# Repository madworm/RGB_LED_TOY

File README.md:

RGB_LED_TOY
===========

LAYOUT FILES: LED ring board with 8 WS2812B RGB LEDs driven by an ATmega168-20AU TQFP-32 7x7 micro controller. KICAD and Gerber files.

You will find code for this project in [this](https://github.com/madworm/rgb_led_toy_test) repository.

---

Before having PC-boards made, please make sure you know about your manufacturer's peculiarities!
Especially drill-sizes and their tolerances may vary too much and give you trouble.

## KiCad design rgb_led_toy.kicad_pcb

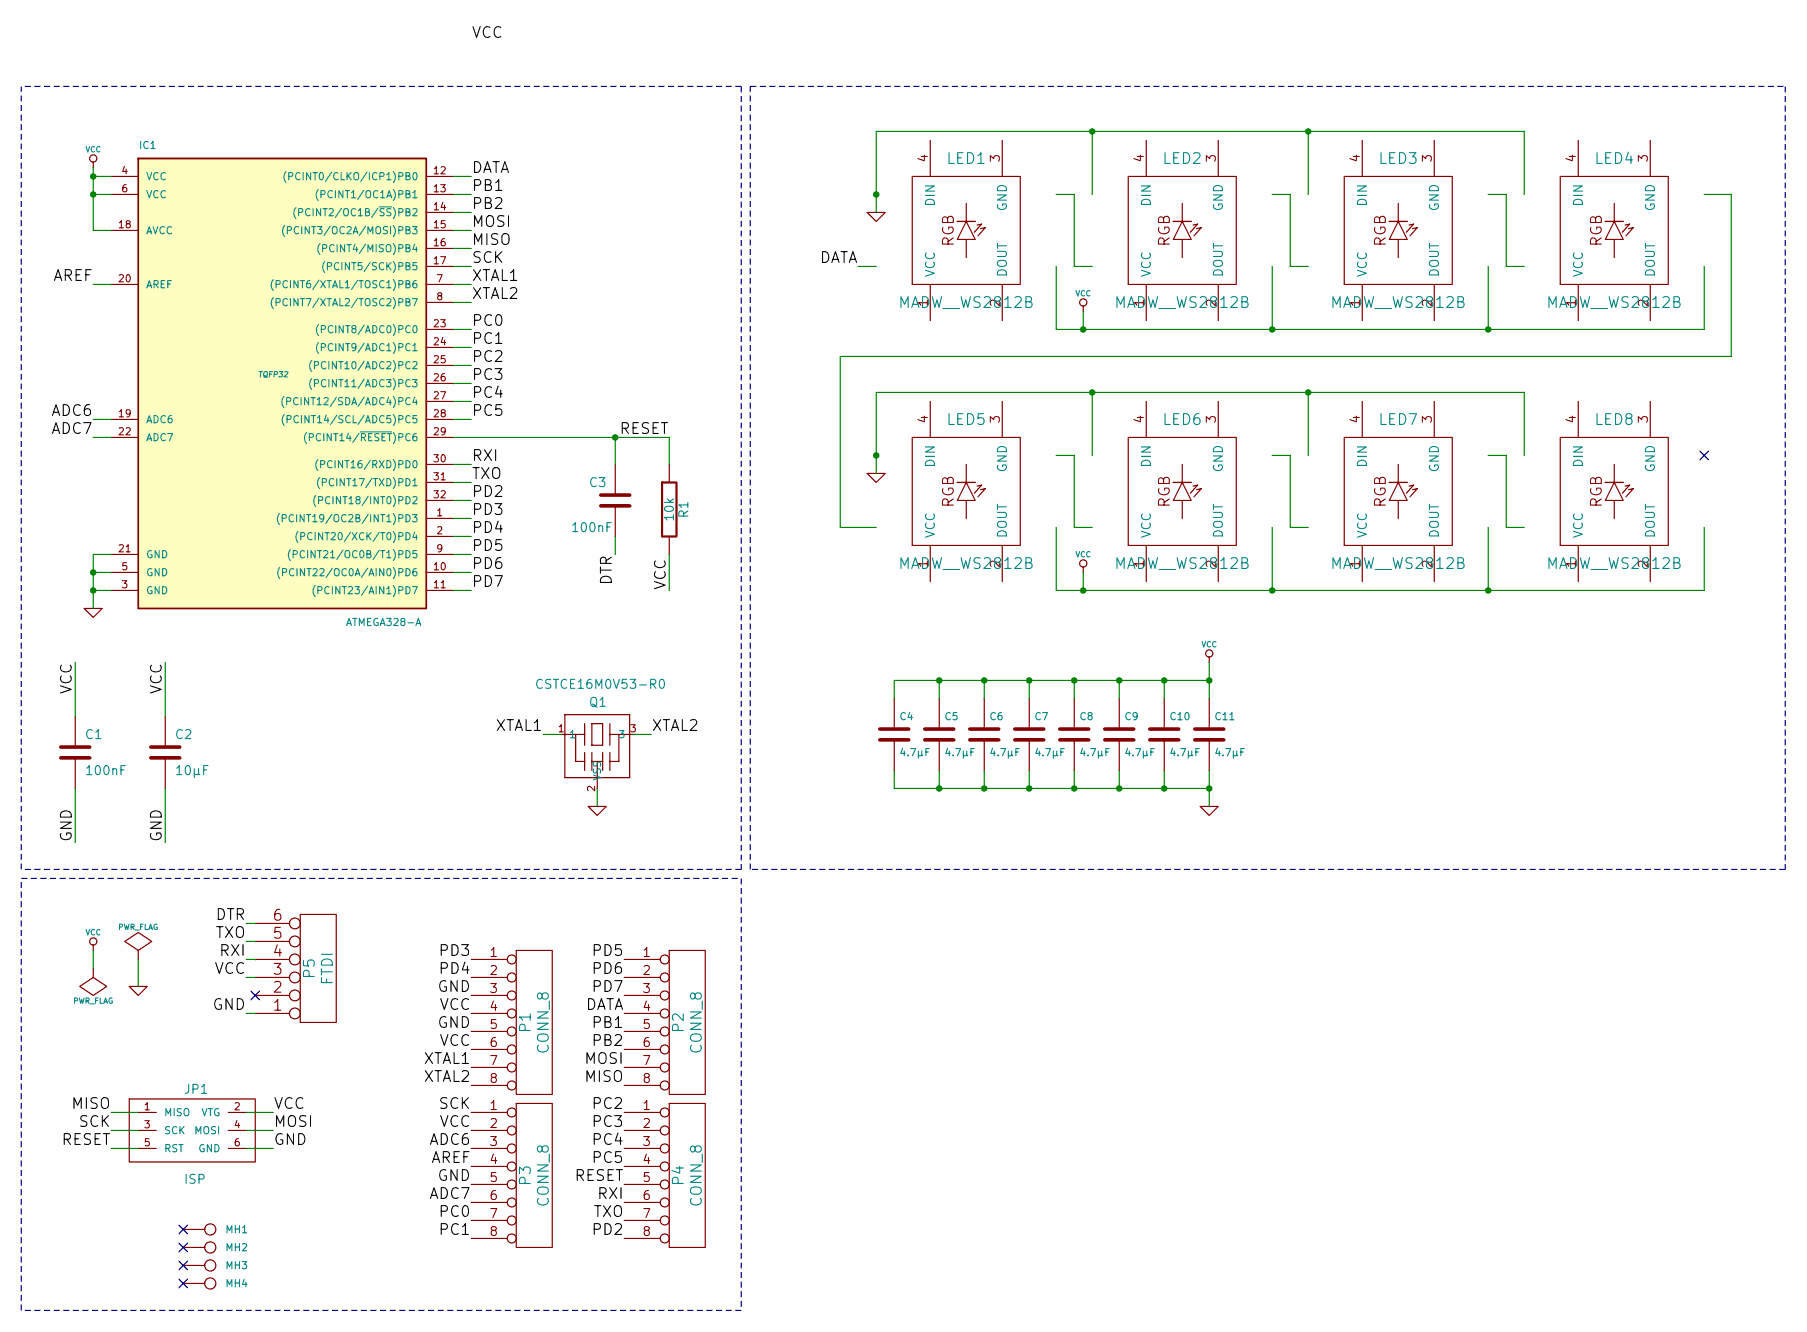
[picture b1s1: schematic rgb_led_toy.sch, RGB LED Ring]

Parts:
C1, C3: 100nF
C2: 10µF
C4, C5, C6, C7, C8, C9, C10, C11: 4.7µF
IC1: ATMEGA328-A; TQFP32
JP1: ISP
LED1, LED2, LED3, LED4, LED5, LED6, LED7, LED8: MADW__WS2812B
MH1, MH2, MH3, MH4: CONN_1
P1, P2, P3, P4: CONN_8
P5: FTDI
Q1: CSTCE16M0V53-R0; murata-resonators-CSTLA_T
R1: 10k

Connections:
/ADC6: IC1.19 (ADC6), P3.3
/ADC7: IC1.22 (ADC7), P3.6
/AREF: IC1.20 (AREF), P3.4
/DATA: IC1.12 ((PCINT0/CLKO/ICP1)PB0), LED1.4 (DIN), P2.4
/DTR: C3.2, P5.6
/MISO: IC1.16 ((PCINT4/MISO)PB4), JP1.1 (MISO), P2.8
/MOSI: IC1.15 ((PCINT3/OC2A/MOSI)PB3), JP1.4 (MOSI), P2.7
/PB1: IC1.13 ((PCINT1/OC1A)PB1), P2.5
/PB2: IC1.14 ((PCINT2/OC1B/~SS~)PB2), P2.6
/PC0: IC1.23 ((PCINT8/ADC0)PC0), P3.7
/PC1: IC1.24 ((PCINT9/ADC1)PC1), P3.8
/PC2: IC1.25 ((PCINT10/ADC2)PC2), P4.1
/PC3: IC1.26 ((PCINT11/ADC3)PC3), P4.2
/PC4: IC1.27 ((PCINT12/SDA/ADC4)PC4), P4.3
/PC5: IC1.28 ((PCINT14/SCL/ADC5)PC5), P4.4
/PD2: IC1.32 ((PCINT18/INT0)PD2), P4.8
/PD3: IC1.1 ((PCINT19/OC2B/INT1)PD3), P1.1
/PD4: IC1.2 ((PCINT20/XCK/T0)PD4), P1.2
/PD5: IC1.9 ((PCINT21/OC0B/T1)PD5), P2.1
/PD6: IC1.10 ((PCINT22/OC0A/AIN0)PD6), P2.2
/PD7: IC1.11 ((PCINT23/AIN1)PD7), P2.3
/RESET: C3.1, IC1.29 ((PCINT14/~RESET~)PC6), JP1.5 (RST), P4.5, R1.1
/RXI: IC1.30 ((PCINT16/RXD)PD0), P4.6, P5.4
/SCK: IC1.17 ((PCINT5/SCK)PB5), JP1.3 (SCK), P3.1
/TXO: IC1.31 ((PCINT17/TXD)PD1), P4.7, P5.5
/XTAL1: IC1.7 ((PCINT6/XTAL1/TOSC1)PB6), P1.7, Q1.1
/XTAL2: IC1.8 ((PCINT7/XTAL2/TOSC2)PB7), P1.8, Q1.3
GND: C1.2, C2.2, C4.2, C5.2, C6.2, C7.2, C8.2, C9.2, C10.2, C11.2, IC1.3 (GND), IC1.5 (GND), IC1.21 (GND), JP1.6 (GND), LED1.3 (GND), LED2.3 (GND), LED3.3 (GND), LED4.3 (GND), LED5.3 (GND), LED6.3 (GND), LED7.3 (GND), LED8.3 (GND), P1.3, P1.5, P3.5, P5.1, Q1.2 (VSS)
Net-<LED1-Pad2>: LED1.2 (DOUT), LED2.4 (DIN)
Net-<LED2-Pad2>: LED2.2 (DOUT), LED3.4 (DIN)
Net-<LED3-Pad2>: LED3.2 (DOUT), LED4.4 (DIN)
Net-<LED4-Pad2>: LED4.2 (DOUT), LED5.4 (DIN)
Net-<LED5-Pad2>: LED5.2 (DOUT), LED6.4 (DIN)
Net-<LED6-Pad2>: LED6.2 (DOUT), LED7.4 (DIN)
Net-<LED7-Pad2>: LED7.2 (DOUT), LED8.4 (DIN)
VCC: C1.1, C2.1, C4.1, C5.1, C6.1, C7.1, C8.1, C9.1, C10.1, C11.1, IC1.4 (VCC), IC1.6 (VCC), IC1.18 (AVCC), JP1.2 (VTG), LED1.1 (VCC), LED2.1 (VCC), LED3.1 (VCC), LED4.1 (VCC), LED5.1 (VCC), LED6.1 (VCC), LED7.1 (VCC), LED8.1 (VCC), P1.4, P1.6, P3.2, P5.3, R1.2

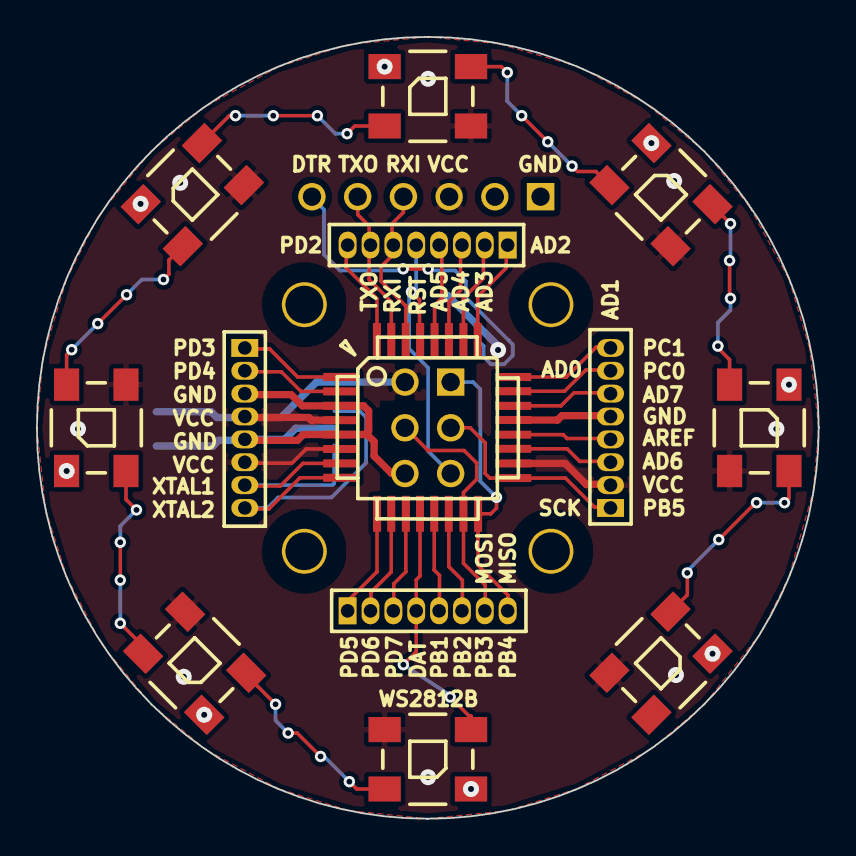
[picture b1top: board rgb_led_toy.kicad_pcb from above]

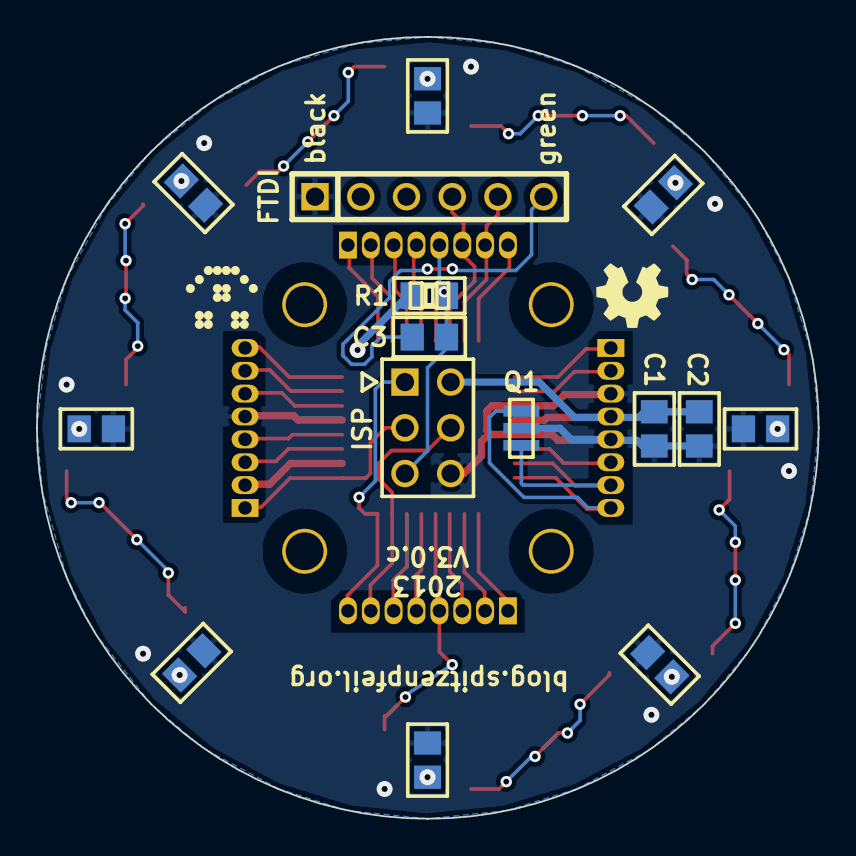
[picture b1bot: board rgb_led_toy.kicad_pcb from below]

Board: 2 copper layers, 43.4 x 43.4 mm, 34 parts (17 on the bottom side), 36 nets.

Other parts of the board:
G1: OSHW-logo_silkscreen_4mm
G2: LED_smile_silkscreen_4mm

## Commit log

2010-01-05 init
2010-01-05 upgraded to V.1.2: voltage regulator, isp_e jumpers.
2010-01-05 modified: rgb_led_toy-schematic.pdf modified: rgb_led_toy-schematic.svg modified: rgb_led_toy.000 modified: rgb_led_toy.bak modified: rgb_led_toy.brd modified: rgb_led_toy.cache.dcm modified: rgb_led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
2010-01-05 fixed silkscreen error. tantalum caps are polarized and need a + mark
2010-01-06 Fixed some silkscreen errors again.
2010-01-06 Added copper fill. Upped to V.1.21
2010-01-06 Changed the zone filling a bit.
2010-01-06 'Exclude Edges_Pcb layer' is necessary to keep the DRC bot happy.
2010-01-06 Another attempt to please the DRC bot. KICAD produces little tiny blobs and gaps in the copper fill that the bot doesn't like.
2010-01-06 This time the BatchPCB DRC bot is happy. Ordered 2 prototypes of V.1.21
2010-01-06 The drill file format was wrong it seemed. Changed to: units: inches, zeros format: suppress leading zeros, precision: 2:4, drill origin: absolute
2010-02-19 new file: rgb_led_toy-BOM.ods.zip new file: rgb_led_toy-BOM.txt
    added BOM
2010-03-02 modified: rgb_led_toy-BOM.ods.zip
2010-04-01 modified: rgb_led_toy-BOM.ods.zip modified: rgb_led_toy-BOM.txt
    updates
2010-05-17 modified: rgb_led_toy-BOM.ods.zip
    DONE. All parts are here ;-)
2010-08-01 Added a readme file with some info.
2010-09-02 V 1.22 test. Added another set of 3 resistors for more current (I hope). Also remove the ISP_E jumpers. ISP flashing worked with the jumpers bridged last time, so they're useless.
2010-09-05 V1.23 - fixed the LED footprint/wiring for the JELEDHK RGB LEDs (PLCC6 5050). - added the 'more light hack' (3 more resistors) etc etc. - replaced the 6pin headers with 8pin ones - added VCC to the '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
2011-10-05 Renamed the schematic files for consistency with other projects.
2011-10-08 Corrected some .gvp files due to folder renaming.
2011-12-19 Testing feasibility of a ring with 3x MBI5168.
2011-12-20 Version 2.0 alpha with just one MBI5168.
    Let's see if color balancing can be done with software dot correction.
2011-12-20 Fixd the LED numbering scheme.
2011-12-20 Did some 'important' updates to the silkscreen.
2011-12-20 Fixed overlapping text on silkscreen. What else?
2011-12-20 As it's winter now (started to snow today), I added a winter themed .gvp
2011-12-21 Routed V2.0 beta with 3x MBI5168 instead of just one + 3 P-FETs.
2011-12-21 Undid some auto-router badness.
2011-12-23 Beautification of the schematic. No functional changes.
2011-12-27 Added (+) text to the silkscreen for all decoupling caps.
    Seems like I won't get 1206 10µF ceramic caps for cheap this time,
    so I might use up my stash of A3216 (metric) tantalum caps (polarized).
2011-12-27 Replaced the (+) with a simple 'dot'. Looks better, less clutter.
2012-01-06 Added a dual PLCC6-5050 / PLCC2 LED footprint + board rev: 2.0.c
2012-01-06 Moved 2 logos a bit.
2012-01-06 Shifted things around a bit.
2012-01-06 Added another 8x 0805 LEDs (just all on/off). Board rev: 2.0.d
2012-01-07 Silkscreen tweaks... moving vias around...
2012-01-07 Moved the auxiliary 0805 LEDs to a hardware PWM pin.
2012-01-10 Fixed the swapped GND / DTR pins on the FTDI header.
    This error was introduced in 80289ae848025eb0ddf43d037901b7deda3aad72.
    Commit a7f8c3d605fc21b7360958f8f994f2175ff54792 is still OK, but a
    different board revision as well.
2012-01-11 Moved 'led0' to a hardware PWM pin that is actually free to use.
2012-01-11 Added some weird stuff to the silkscreen again.
2012-01-14 Miniscule visual tweak to the schematic.
2012-01-15 Minor mods + added 'Lord Helmet' as well ;-)
2012-03-14 Added a BOM/assembly .pdf file (hybrid mode).
2012-03-14 Fixed a line-width problem.
2012-03-14 Added a note regarding RGB LEDs and 250°C
2012-03-17 Added an alternative for the MBI5168 to the BOM: STP08CP05MTR
2012-03-17 Corrected the page format from "letter" to "A4" for the BOM file.
2012-04-06 Added 'push.sh'
2012-04-26 Upgraded the BOM .pdf file.
2012-05-08 Added the TSOP38238 for IR reception to INT0 + some silkscreen art.
2012-05-09 Silkscreen tweaks.
2012-05-09 Shifted a header a bit + shell-script mods.
2012-05-09 Removed useless line in .gvp files. Why does it store that...
2012-05-09 Fixed a 'silly trace'.
2012-05-09 Fixed the back silkscreen. As usual right after the order...
2012-05-09 Updated the bom.
2012-05-09 TSOP38238 rotated 180° so it can be flat on the board looking upwards.
2012-05-09 Upped the version to 2.0.f
2012-05-10 Shifted a few parts to fix the silkscreen.
2012-05-10 Moved a via due to silkscreen interference.
2012-05-11 Moved the OE pin to a hardware PWM pin (PD5).
2012-05-11 Moved the OE pin to TIMER2 PWM (PD3) for increased frequency.
2012-05-12 Added 3x fire symbols to the silkscreen (LED drivers do get hot).
2012-05-12 Added a no-net copper pour to spread the heat a bit better.
2012-05-12 Redid the copper pour outline. Should panelize better.
2012-05-13 'power'-net via changed from 35:25 to 35:20 (wider anular ring).
2012-05-17 Added the MBI5167 as an alternative to the BOM.
2012-05-17 Forgot an empty line.
2012-05-24 Experimenting with 'gerbmerge' and panelization.
2012-05-24 Added drill holes in the break-away tabs.
2012-05-31 Tweaks.
    Forgot to give unique names to the break-away drill holes.
    One mounting hole wasn't named correctly.
2012-06-02 Filled .gitignore with meaningful entries.
2012-06-02 Removed files now covered by .gitignore
2012-06-02 Updated .gitignore
2012-07-22 Added some assembly-tips.
2012-07-26 Updated 'assembly-tips.txt'
2012-09-03 Cleaned up the .gvp files...
2012-11-25 gerbmerge: + missing fiducial. Don't use silkscreen / mask subtraction in KiCad.
2013-01-17 Added README.md
2013-01-23 Increased drill size for pin-headers to 40mil.
    Did NOT recreate gerber files!
2013-01-23 Recreated the gerber files (40mil drill size issue).
2013-01-23 Changed library path, so it doesn't use a symlink anymore.
2013-02-11 Added a step-by-step assembly guide for V2.1 boards. See Docs folder.
2013-04-23 Updated 'README.md'
2013-05-13 Updated assembly instructions for V2.1 boards.
2013-06-27 Renamed a file in ./Docs/ folder.
2013-06-28 Converted to new kicad board format.
2013-09-20 V3.0 doodles.
2013-09-21 Might be a first working V3.0
2013-09-21 Some tweaks.
2013-09-21 LED-string now goes clockwise. Added 1.27mm headers for all MCU pins.
2013-09-22 Tweaks: silkscreen, copper p. cutouts, 8mil min trace width, 16MHz reso.
2013-09-24 Updated 'README.md'.
2013-09-29 Had to fix the resonator footprint (library part was off).
2013-09-29 Some cleanup after changing the WS2812B symbol in my library.
2013-10-18 Added 'Docs' + readme updated.
2014-02-23 Forgot to update the board revision to 3.0.c on the layout page properties.
2014-07-27 Added a simplified bill of materials file.
2014-11-02 Added datasheet + 'hints.txt'.
